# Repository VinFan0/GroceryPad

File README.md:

# GroceryPad
## Overview

GroceryPad is a compact display for shopping lists, to-do lists, reminders, and more. The on-board ESP32 microcontroller acts as a display driver, as well as hosts an HTTP server on the local network. Data sent to the server in the form of an HTTP POST is parsed and sent to the 3.7" Epaper module.

GroceryPad is initially designed to sync with a list managed in the Reminders app of an iOS device. In this configuration, the iOS device sends a scheduled HTTP POST with the contents of the reminder/list to the server hosted by the GroceryPad device. 

**R1.1-A changes**
- Power switch
- Android companion app for checklist display

### Hardware Requirements
- [ESP32-C3 Supermini microcontroller](https://www.espboards.dev/esp32/esp32-c3-super-mini/)
- [WeAct 3.7" Epaper module](https://github.com/WeActStudio/WeActStudio.EpaperModule)
- [HiLetgo TP4056 USB-C Lithium Battery Charging Module](https://www.amazon.com/HiLetgo-Lithium-Charging-Protection-Functions/dp/B07PKND8KG)
- [3.7V Rechargeable Lithium Polymer battery](https://www.amazon.com/dp/B0CNLPK1F8?ref=ppx_yo2ov_dt_b_fed_asin_title&th=1)
- 3mm indicator LED
- Smartphone (for automatic list syncing)

### Software Requirements
Code is uploaded to the board via ArduinoIDE, which can be downloaded here: [Download ArduinoIDE](https://www.arduino.cc/en/software/)

To connect with the ESP32 board, you must also install the ESP32 board. Instructions are available on the [espressif website](https://docs.espressif.com/projects/arduino-esp32/en/latest/installing.html)

For the automatic syncing with a smartphone list, an additional app must be used to schedule the sending of the HTTP POST. iPhones can use the Shortcuts app, which is installed by default on all devices running iOS 13 or later. For Android, I recommend [Tasker](https://play.google.com/store/apps/details?id=net.dinglisch.android.taskerm&hl=en_US). Steps for setting this up are found under the **Setup** section.

## Setup
For the GroceryPad device to function, a connection to a local WiFi network is required. Included with the Arduino sketch is a `ssid_options.h` file. This header file can be used to define the SSID and password variables the ESP32 will use to connect to WiFi. Fill in the `ssid` and `password` strings with your local WiFi details. *Note: The ESP32 is only compatible with 2.4 GHz WiFi.*

Once the `ssid_options.h` file is filled in, the code can be compiled and loaded onto the microcontroller. If the connection is successfull, the microcontroller will print a "WiFi Connected" message to the console. Along with the success message, the IP address will also be printed. Take note of this IP address, as it will be required in sending the HTTP POST messages.

### iOS Shortcuts Configuration
Setting up the Shortcut to periodically send the HTTP POST is not complicated, but can take some time to figure out if you are new to workflow automations or Apple Shortcuts specifically. Here is provided a simple walkthrough of setting up the Shortcut.

Items necessary to creating the Shortcut:
- Apple Shortcuts app is installed
- The IP address of the ESP32 HTTP server
- A Reminder list on the same iOS device

**Step 1**

**Sending messages manually** with curl

Messages can also be sent to the device manually using a linux-style terminal and the `curl` command. Basic syntax is

`curl -X POST http://<ESP IP ADDRESS>/reminder -H "Content-Type: application/json" -d '<MESSAGE CONTENT>'`

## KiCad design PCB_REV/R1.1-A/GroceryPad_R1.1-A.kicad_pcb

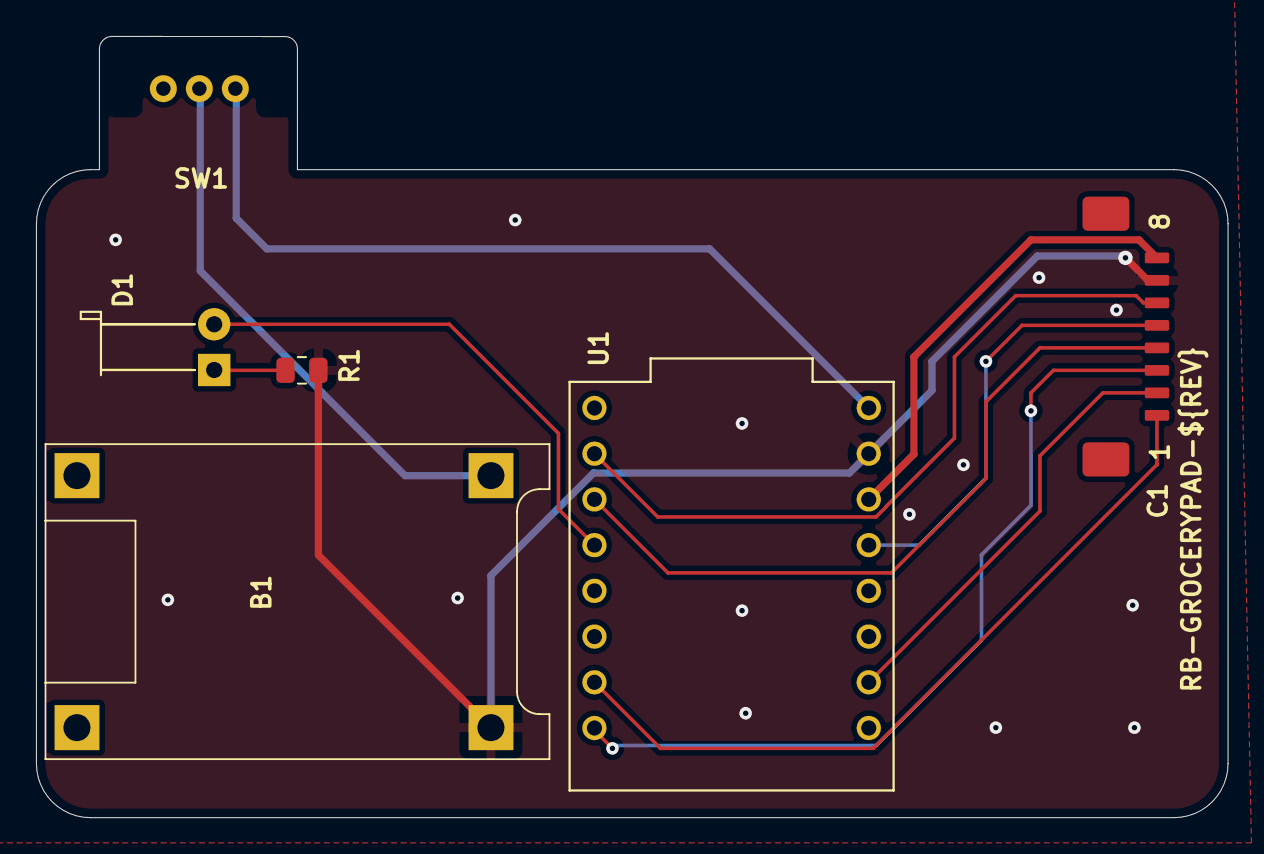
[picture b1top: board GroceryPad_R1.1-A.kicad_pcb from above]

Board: 2 copper layers, 66.2 x 43.4 mm, 6 parts (0 on the bottom side), 12 nets.

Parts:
B1: HiLetgo TP4056 BOB
C1: 1.25mm_8P_WireToBoard
D1: LED; LED_D3.0mm_Horizontal_O6.35mm_Z2.0mm
R1: 2k; R_0805_2012Metric
SW1: SW_SPDT_312; SPDT Slide Switch
U1: ESP32-C3_SUPERMINI_TH; MODULE_ESP32-C3_SUPERMINI_TH

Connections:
3V3: C1.8 (VCC), U1.3.3 (3V3)
5V: B1.3 (OUT+), SW1.1 (B)
BUSY: C1.1 (BUSY), U1.20 (GPIO20)
CS: C1.4 (CS), U1.7 (GPIO7)
DC: C1.3 (DC), U1.21 (GPIO21)
GND: B1.4 (OUT-), C1.7 (GND), R1.2, U1.G (GND)
unnamed: D1.1 (K), R1.1
RES: C1.2 (RES), U1.1 (GPIO1)
SCL: C1.5 (SCL), U1.4 (GPIO4)
SDA: C1.6 (SDA), U1.6 (GPIO6)
STATUS: D1.2 (A), U1.8 (GPIO8)
SW_5V: SW1.2 (C), U1.5V

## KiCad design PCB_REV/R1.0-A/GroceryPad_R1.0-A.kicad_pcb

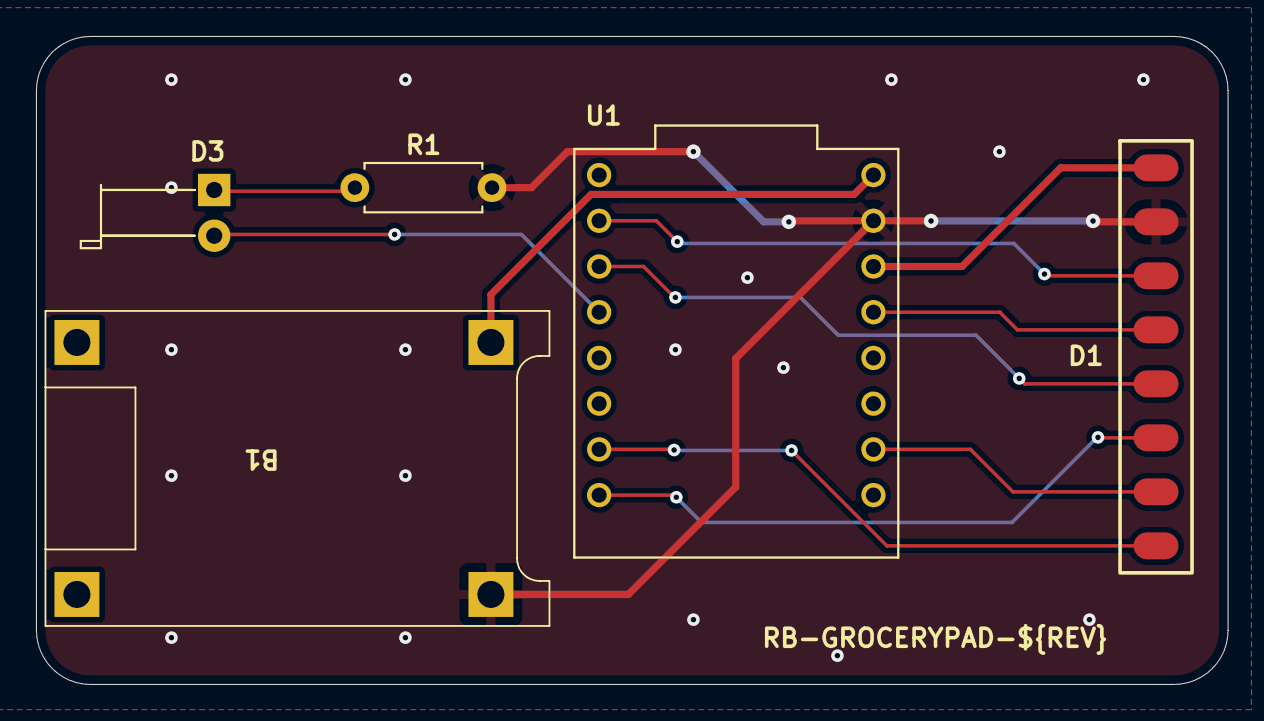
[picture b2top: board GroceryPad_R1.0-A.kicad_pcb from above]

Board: 2 copper layers, 66.2 x 36.0 mm, 5 parts (0 on the bottom side), 11 nets.

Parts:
B1: HiLetgo TP4056 BOB
D1: WeAct Studio 3.7 Epaper Module
D3: LED; LED_D3.0mm_Horizontal_O6.35mm_Z2.0mm
R1: 2k; R_Axial_DIN0207_L6.3mm_D2.5mm_P7.62mm_Horizontal
U1: ESP32-C3_SUPERMINI_TH; MODULE_ESP32-C3_SUPERMINI_TH

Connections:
3V3: D1.8 (VCC), U1.3.3 (3V3)
5V: B1.3 (OUT+), U1.5V
BUSY: D1.1 (BUSY), U1.20 (GPIO20)
CS: D1.4 (CS), U1.7 (GPIO7)
DC: D1.3 (DC), U1.21 (GPIO21)
GND: B1.4 (OUT-), D1.7 (GND), R1.2, U1.G (GND)
unnamed: D3.1 (K), R1.1
RES: D1.2 (RES), U1.1 (GPIO1)
SCL: D1.5 (SCL), U1.4 (GPIO4)
SDA: D1.6 (SDA), U1.6 (GPIO6)
STATUS: D3.2 (A), U1.8 (GPIO8)

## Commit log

2025-10-28 Readme
2025-10-28 .ignore
2025-10-28 Readme update
2025-10-28 Ingore Libraries
2025-10-28 Remove Libraries
2025-10-28 Updated GroceryPad
2025-10-28 IGnore update
2025-10-28 Re-add libraries
2025-10-28 Cleaned libraries, empty POST functionality
2025-10-28 Created network.h
2025-10-28 Hotspot and cleaned setup
2025-10-29 Fixed network.h issues
2025-10-29 Line overflow protection
2025-10-29 Full ssid_options.h file
2025-11-23 Configured for ESP32-C3 device
2025-11-23 Working with battery power
2025-11-24 PCB R1.0-A
2025-11-27 TP4056 breakout footprint
2025-11-27 R1.0- A sent to production
2025-12-04 R1.0-A final
2025-12-04 Ignore ssid_options.h
2025-12-04 Genertic SSID options
    Removed unused network definitions and added local network option.
2025-12-04 WiFi reconnect cycle, 5 second delay
2025-12-04 Better WiFi recovery
2025-12-05 Enhance README with project details and setup guide
    Expanded README to include detailed project overview, hardware and software requirements, setup instructions, and iOS Shortcuts configuration.
2025-12-05 File organization
2025-12-05 Remove Arduino directory and README update
2025-12-05 Printing files with foam spacer
2025-12-12 ignore libraries
2025-12-12 Multi-network auto join
2025-12-12 update ignores
2025-12-12 ignore fix1
2025-12-12 ignore fix2
2025-12-12 Ignores
2025-12-12 Network Credentials Header File
    Enter known network credentials here
2025-12-15 Un ignore libraries
2025-12-15 Arduino sketch version 1.0 and 1.1
2025-12-17 BLE peripheral and module breakout files
2025-12-17 BLE functionality
2025-12-17 Characteristics 1/3/4, Display update working
2025-12-18 Working list sync and add/delete display updates
2025-12-28 Check/Uncheck strike through
2025-12-28 Initial V1.2 sketch
2025-12-29 Partial Window updates for adding items and check/unckeck
2025-12-31 Power switch and case update
2025-12-31 README.md R1.1-A partial
